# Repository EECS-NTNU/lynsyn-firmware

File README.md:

# Lynsyn

Lynsyn is a device designed to perform application power profiling of ARM Cortex A based systems.  For more information, see the [Lynsyn firmware wiki](https://github.com/EECS-NTNU/lynsyn-firmware/wiki) and the [Lynsyn host software wiki](https://github.com/EECS-NTNU/lynsyn-host-software/wiki).

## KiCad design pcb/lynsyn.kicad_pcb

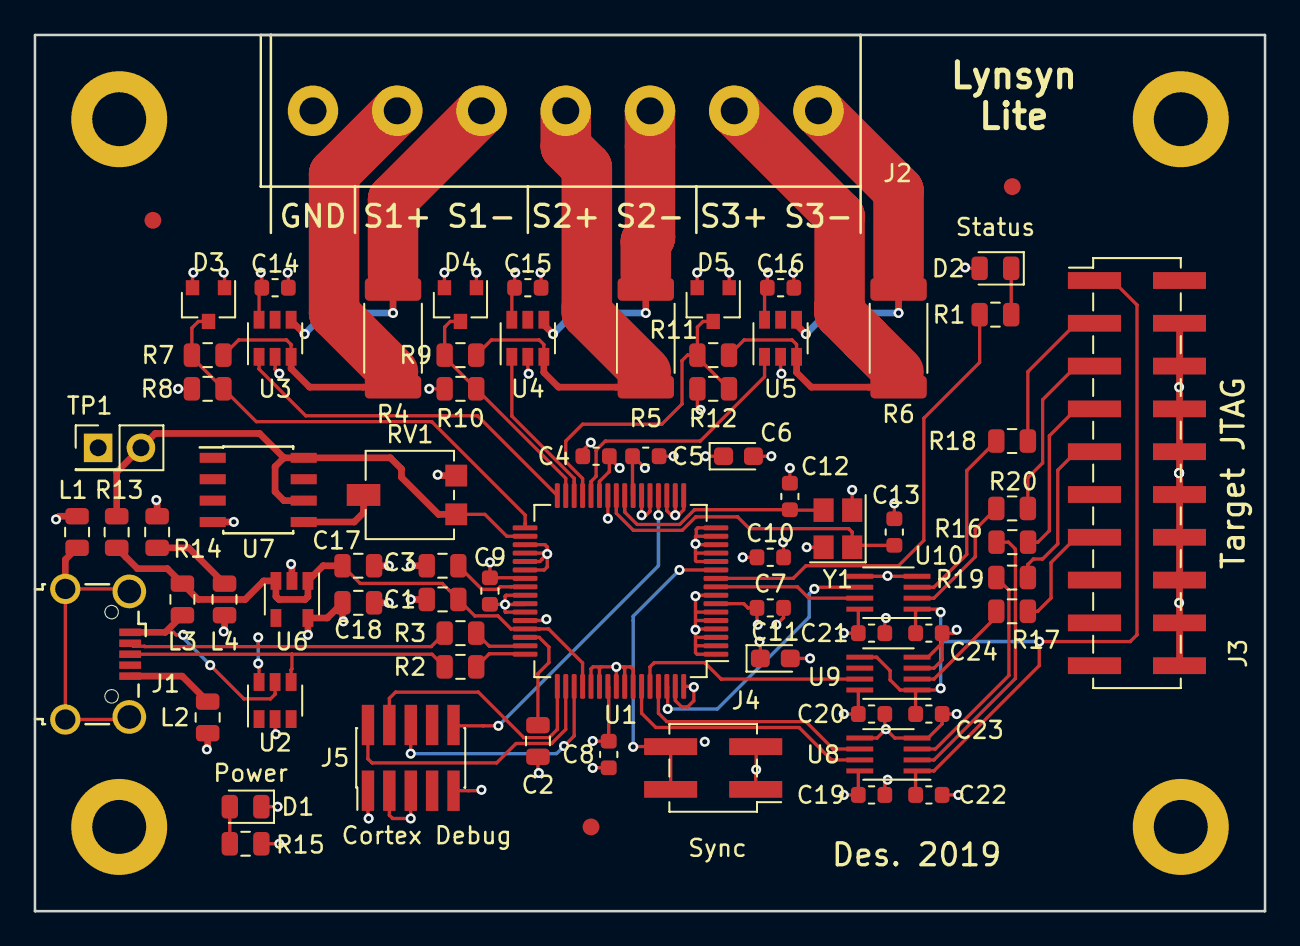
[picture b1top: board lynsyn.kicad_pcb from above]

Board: 4 copper layers, 73.0 x 52.0 mm, 71 parts (0 on the bottom side), 54 nets.

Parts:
C1: 4.7u; C_0805_2012Metric
C2, C3, C17, C18: 1u; C_0805_2012Metric
C4, C5, C7, C8, C9, C10, C14, C15, C16, C19, C20, C21, C22, C23, C24: 100n; C_0603_1608Metric
C6, C11: 10u; CP_EIA-2012-12_Kemet-R
C12, C13: 12p; C_0603_1608Metric
D1: Red; LED_0805_2012Metric
D2: Green; LED_0805_2012Metric
D3, D4, D5: BAT54S; SOT-23
J1: USB Micro-B; USB_Micro-B_Wuerth_629105150521_CircularHoles
J2: power_sensor; TERMINAL_BLOCK_5mm
J3: Conn_ARM_JTAG_SWD_20; PinHeader_2x10_P2.54mm_Vertical_SMD
J4: Sync; PinHeader_2x02_P2.54mm_Vertical_SMD
J5: Cortex Debug; PinHeader_2x05_P1.27mm_Vertical_SMD
L1, L2, L3, L4: Ferrite_Bead; L_0805_2012Metric
R1, R15: 91; R_0805_2012Metric
R2, R3: 15; R_0805_2012Metric
R4, R5, R6: Rs; R_2512_6332Metric
R7, R9, R11: 82k; R_0805_2012Metric
R8, R10, R12: 10k; R_0805_2012Metric
R13: 3.6k; R_0805_2012Metric
R14: 1; R_0805_2012Metric
R16, R17, R18, R19, R20: 100; R_0805_2012Metric
RV1: 10k; Potentiometer_Vishay_TS53YL_Vertical
TP1: TEST; PinHeader_2x01_P2.54mm_Vertical
U1: EFM32GG332F1024; TQFP-64_10x10mm_P0.5mm
U2: IP4220CZ6; SOT-23-6
U3, U4, U5: LMP8640; SOT-23-6
U6: MIC5504-3.3YM5; SOT-23-5
U7: LT1009; SOIC-8_3.9x4.9mm_P1.27mm
U8, U9, U10: 74LVC2T45; SSOP-8_2.95x2.8mm_P0.65mm
Y1: 48MHz; Crystal_SMD_3225-4Pin_3.2x2.5mm

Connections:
+3.3VA: C4.1, C5.1, C6.1, C14.1, C15.1, C16.1, D3.2, D4.2, D5.2, R14.1, U1.23, U1.27, U3.6, U4.6, U5.6
+3V3: C7.1, C8.1, C9.1, C10.1, C11.1, C18.1, C19.1, C20.1, C21.1, D2.2, J5.1, L4.2, R15.1, U1.7, U1.26, U1.39, U1.55, U6.5, U8.8, U9.8, U10.8
/Current monitor/ADC0: U1.28, U5.1
/Current monitor/ADC1: D5.3, R11.2, R12.1, U1.29
/Current monitor/ADC2: U1.30, U4.1
/Current monitor/ADC3: D4.3, R9.2, R10.1, U1.31
/Current monitor/ADC4: U1.32, U3.1
/Current monitor/ADC5: D3.3, R7.2, R8.1, U1.33
/JTAG/JTAG_out_VREF: C22.1, C23.1, C24.1, J3.1, U8.1, U9.1, U9.5, U10.1
/MCU/CLK0: U1.61, U8.6
/MCU/MCU_D+: R2.1, U1.48
/MCU/MCU_D-: R3.1, U1.47
/MCU/RX0: U1.60, U9.7
/MCU/SRST: U1.62, U10.6
/MCU/TX0: U1.59, U8.7
/MCU/TX1: U1.9, U10.7
/MCU/USB_D+: J1.3, R2.2, U2.4
/MCU/USB_D-: J1.2, R3.2, U2.6
AREF: R13.2, RV1.3, TP1.2, U1.34, U7.6, U7.8
GND: C1.2, C2.2, C3.2, C4.2, C5.2, C6.2, C7.2, C8.2, C9.2, C10.2, C11.2, C12.2, C13.2, C14.2, C15.2, C16.2, C17.2, C18.2, C19.2, C20.2, C21.2, C22.2, C23.2, C24.2, D1.1, D3.1, D4.1, D5.1, J2.1, J3.4, J3.6, J3.8, J3.10, J3.12, J3.14, J3.16, J3.18, J3.20, J4.1, J4.3, J5.3, J5.5, J5.9, L1.2, L2.2, R8.2, R10.2, R12.2, RV1.1, TP1.1, U1.1, U1.2, U1.3, U1.4, U1.5, U1.6, U1.8, U1.12, U1.13, U1.14, U1.15, U1.16, U1.17, U1.18, U1.19, U1.21, U1.22, U1.35, U1.36, U1.37, U1.38, U1.41, U1.42, U1.43, U1.44, U1.53, U1.54, U1.56, U1.57, U1.58, U1.63, U1.64, U2.2, U3.2, U4.2, U5.2, U6.2, U7.4, U8.4, U8.5, U9.3, U9.4, U10.4, U10.5, Y1.2, Y1.4
unnamed: C2.1, U1.46
unnamed: C3.1, U1.40
unnamed: C12.1, U1.24, Y1.3
unnamed: C13.1, U1.25, Y1.1
unnamed: D1.2, R15.2
unnamed: D2.1, R1.2
unnamed: J1.1, L3.2, U2.5
unnamed: J1.5, L2.1
unnamed: J1.6, L1.1
unnamed: J2.2, R4.1, R7.1, U3.3
unnamed: J2.3, R4.2, U3.4
unnamed: J2.4, R5.1, R9.1, U4.3
unnamed: J2.5, R5.2, U4.4
unnamed: J2.6, R6.1, R11.1, U5.3
unnamed: J2.7, R6.2, U5.4
unnamed: J3.3, R18.2
unnamed: J3.5, R20.2
unnamed: J3.7, R16.2
unnamed: J3.9, R19.2
unnamed: J3.13, R17.2
unnamed: J4.2, J4.4, U1.11
unnamed: J5.2, U1.50
unnamed: J5.4, U1.49
unnamed: J5.6, U1.51
unnamed: J5.10, U1.20
unnamed: L4.1, R14.2
unnamed: R1.1, U1.10
unnamed: R16.1, U8.2
unnamed: R17.1, U9.2
unnamed: R18.1, U10.3
unnamed: R19.1, U8.3
unnamed: R20.1, U10.2
unnamed: RV1.2, U7.5
USB_VBUS: C1.1, C17.1, L3.1, R13.1, U1.45, U1.52, U6.1, U6.3

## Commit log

2019-12-11 Moved to new repository.
2019-12-11 Included FPGA in Makefile
2019-12-11 Fixed silkscreen and added gerber files
2019-12-11 New calibration scheme
2019-12-11 Some updates for Lynsyn Original
2019-12-11 Bugfix with lynsyn_tester and lynsyn original
2019-12-11 Changed back to using lynsyn lite as default target
2019-12-12 Added table view of profile data
2019-12-12 Added number of cores and sensors to the database and csv files. GUI now only shows sensors and cores that are present.
2019-12-12 Added precompiled firmware files
2019-12-12 Lite as default in Makefile
2019-12-12 Fixed FPGA flashing to lynsyn_tester when using original boards.
2019-12-13 Just updated some page information in the schematics. No change to the PCB.
2019-12-18 Bugfix
2019-12-18 Spelling mistake
2020-01-02 Preparations for elfsupport without external dependencies.
2020-01-07 Partly works in windows.
2020-01-07 Minor bugfix windows version.
2020-01-07 Fixed Makefiles to work in both windows and linux.
2020-01-07 Changed elfsupport to qt
2020-01-07 Updated windeploy script
2020-01-08 License
2020-01-08 Added license and copyright to all source files
2020-01-08 Updated windeploy.sh
2020-01-09 Fixed compile warnings in windows. Added new Lynsyn Lite (V3.1) support to lynsyn_tester.
2020-01-09 Much faster elfsupport
2020-01-09 Comments
2020-01-13 Reorganized repository. This is now the private one and has the firmware and pcb. The host software is moved to a public repo.
2020-01-14 Moved jtagdevices to host repo
2020-01-14 Moved PCB to separate repo
2020-01-15 Changed incorrect license information in source files
2020-01-28 Moved calibration from firmware to host
2020-01-28 Removed debug output
2020-03-12 Added support for Cortex A72
2020-04-30 Added support for receiving ARM PIDR values over USB.
2020-04-30 Support for jtag diagnostic log
2021-06-03 Bugfix for version 2
2023-08-24 Create LICENSE
    Added GPL-3 license
